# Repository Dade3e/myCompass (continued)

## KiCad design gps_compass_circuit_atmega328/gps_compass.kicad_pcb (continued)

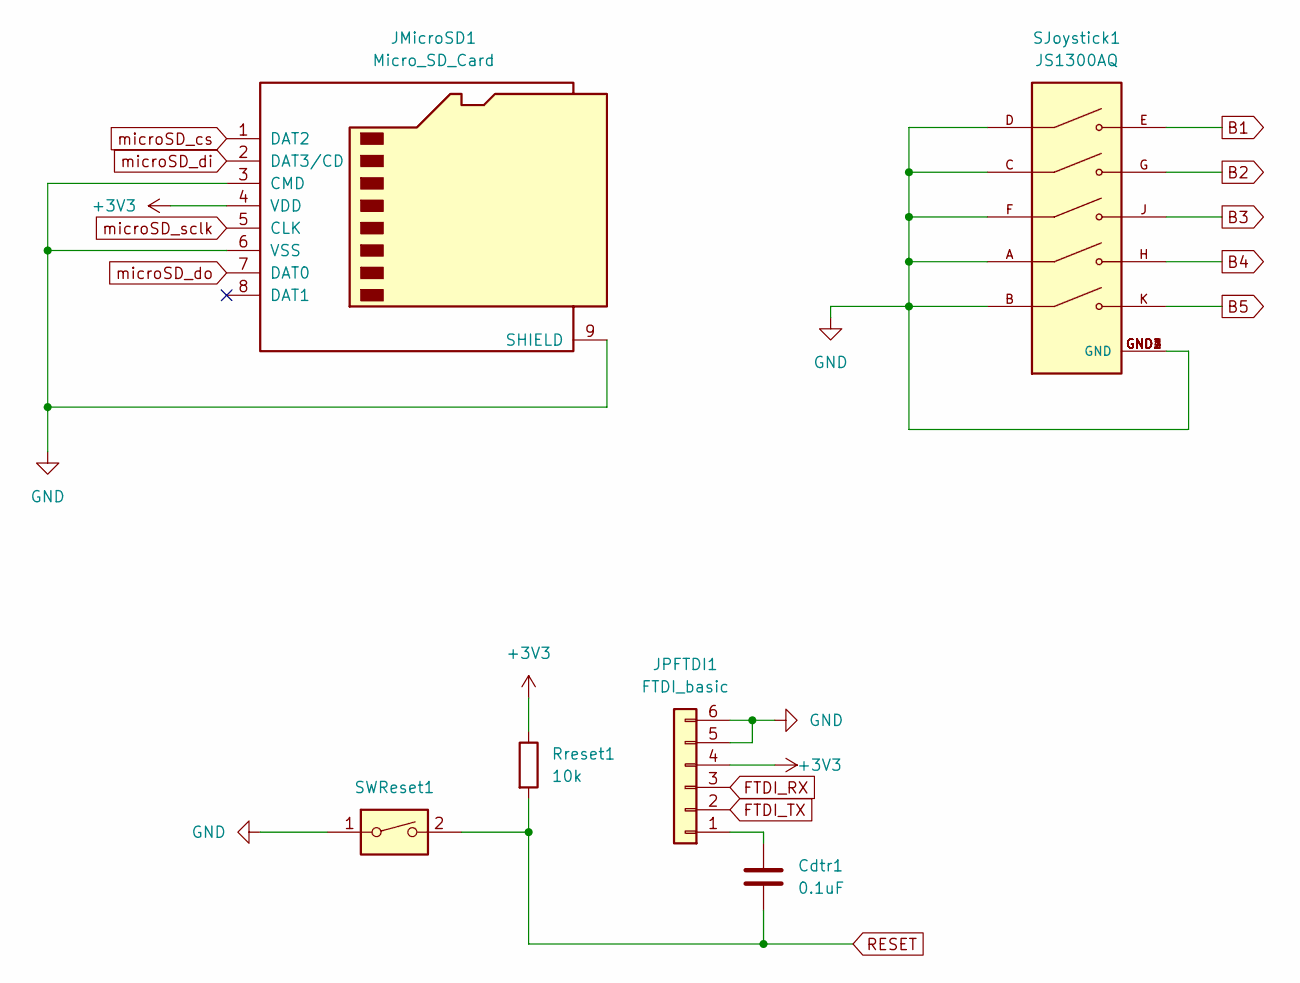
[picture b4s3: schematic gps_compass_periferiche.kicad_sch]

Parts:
Cdtr1: 0.1uF; R_0603_1608Metric
JMicroSD1: Micro_SD_Card; microSD_HC_Molex_47219-2001
JPFTDI1: FTDI_basic; PinSocket_1x06_P2.54mm_Horizontal
Rreset1: 10k; R_0603_1608Metric
SJoystick1: JS1300AQ; SW_JS1300AQ; PARTREV F
SWReset1: SW_Reset; SW_PUSH_6mm

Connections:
+3V3: JMicroSD1.4 (VDD), JPFTDI1.4, Rreset1.1; also elsewhere on the board
B1: SJoystick1.E; also elsewhere on the board
B2: SJoystick1.G; also elsewhere on the board
B3: SJoystick1.J; also elsewhere on the board
B4: SJoystick1.H; also elsewhere on the board
B5: SJoystick1.K; also elsewhere on the board
FTDI_RX: JPFTDI1.3; also elsewhere on the board
FTDI_TX: JPFTDI1.2; also elsewhere on the board
GND: JMicroSD1.3 (CMD), JMicroSD1.6 (VSS), JMicroSD1.9 (SHIELD), JPFTDI1.5, JPFTDI1.6, SJoystick1.A, SJoystick1.B, SJoystick1.C, SJoystick1.D, SJoystick1.F, SJoystick1.GND1 (GND), SJoystick1.GND2 (GND), SJoystick1.GND3 (GND), SJoystick1.GND4 (GND), SWReset1.1; also elsewhere on the board
unnamed: Cdtr1.2, JPFTDI1.1
RESET: Cdtr1.1, Rreset1.2, SWReset1.2; also elsewhere on the board
microSD_cs: JMicroSD1.1 (DAT2); also elsewhere on the board
microSD_di: JMicroSD1.2 (DAT3/CD); also elsewhere on the board
microSD_do: JMicroSD1.7 (DAT0); also elsewhere on the board
microSD_sclk: JMicroSD1.5 (CLK); also elsewhere on the board

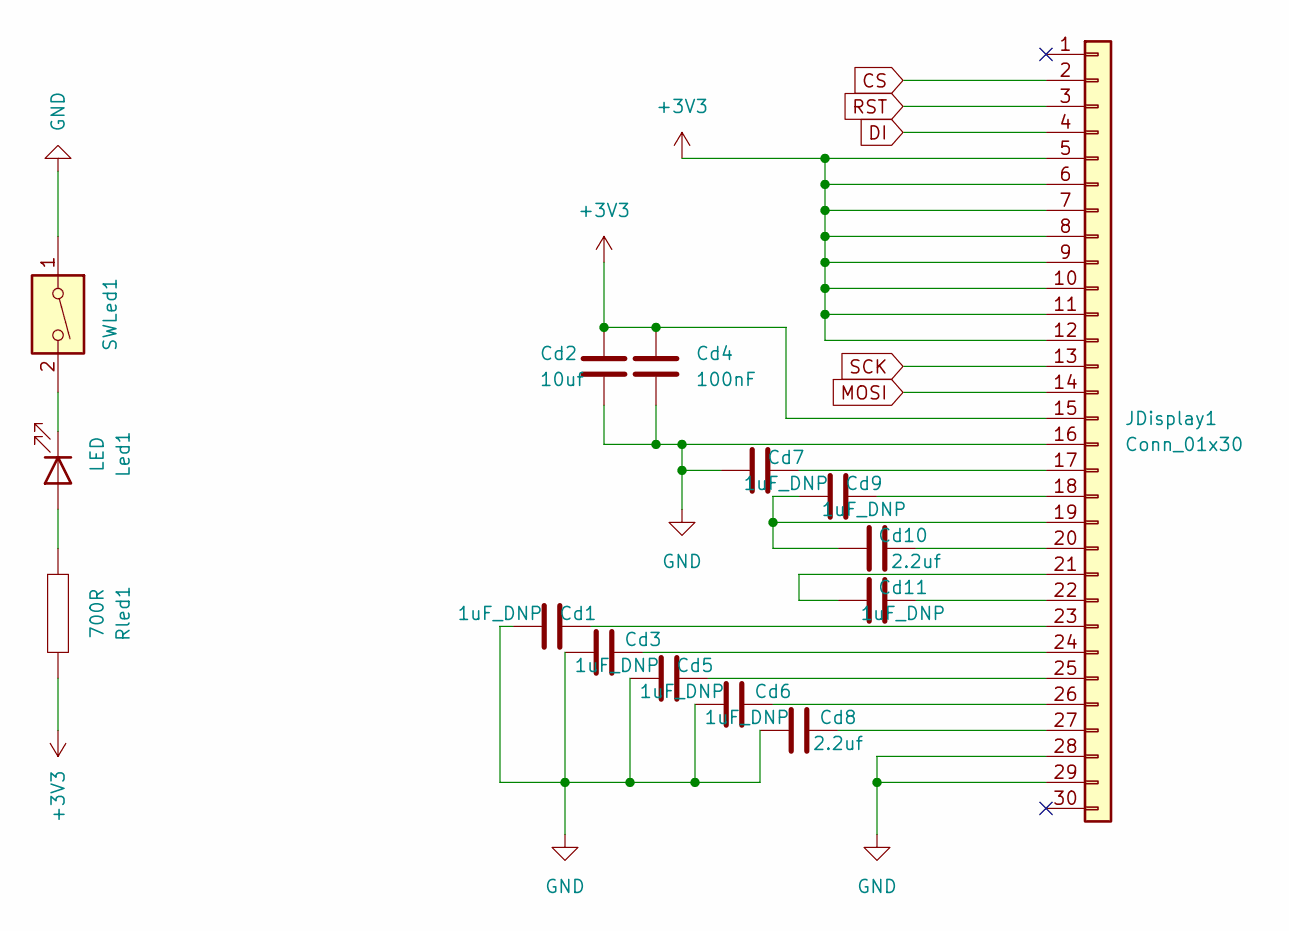
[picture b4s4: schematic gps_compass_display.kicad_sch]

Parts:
Cd1, Cd3, Cd5, Cd6, Cd7, Cd9, Cd11: 1uF_DNP; C_0603_1608Metric
Cd2: 10uf; C_0603_1608Metric
Cd4: 100nF; C_0603_1608Metric
Cd8, Cd10: 2.2uf; C_0603_1608Metric
JDisplay1: Conn_01x30; Hirose_FH12-30S-0.5SH_1x30-1MP_P0.50mm_Horizontal
Led1: LED; LED_D3.0mm
Rled1: 700R; R_0603_1608Metric
SWLed1: SW_Reset; SW_PUSH_6mm

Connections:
+3V3: Cd2.1, Cd4.1, JDisplay1.5, JDisplay1.6, JDisplay1.7, JDisplay1.8, JDisplay1.9, JDisplay1.10, JDisplay1.11, JDisplay1.12, JDisplay1.15, Rled1.2; also elsewhere on the board
CS: JDisplay1.2
DI: JDisplay1.4
GND: Cd1.1, Cd2.2, Cd3.1, Cd4.2, Cd5.1, Cd6.1, Cd7.1, Cd8.1, JDisplay1.16, JDisplay1.28, JDisplay1.29, SWLed1.1; also elsewhere on the board
MOSI: JDisplay1.14
unnamed: Cd1.2, JDisplay1.23
unnamed: Cd3.2, JDisplay1.24
unnamed: Cd5.2, JDisplay1.25
unnamed: Cd6.2, JDisplay1.26
unnamed: Cd7.2, JDisplay1.17
unnamed: Cd8.2, JDisplay1.27
unnamed: Cd9.2, JDisplay1.18
unnamed: Cd9.1, Cd10.1, JDisplay1.19
unnamed: Cd10.2, JDisplay1.20
unnamed: Cd11.1, JDisplay1.21
unnamed: Cd11.2, JDisplay1.22
unnamed: Led1.1 (K), SWLed1.2
unnamed: Led1.2 (A), Rled1.1
RST: JDisplay1.3
SCK: JDisplay1.13

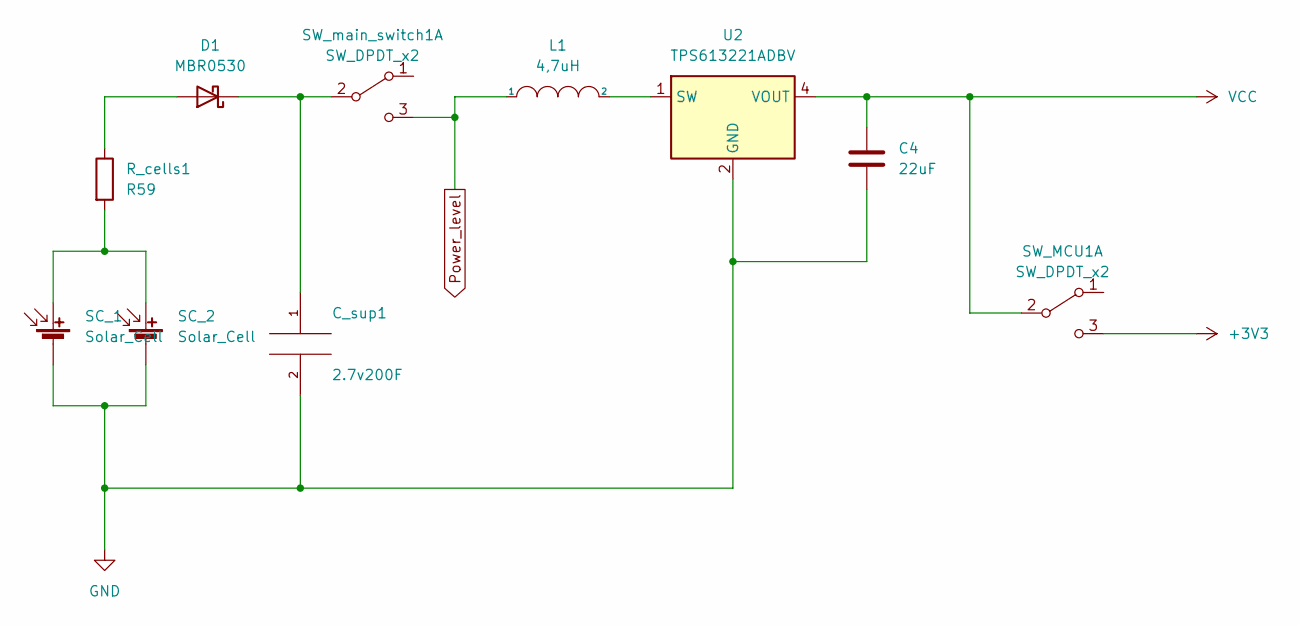
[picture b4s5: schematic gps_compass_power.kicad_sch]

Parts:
C4: 22uF; C_0603_1608Metric
C_sup1: 2.7v200F; C_Rect_L9.0mm_W2.5mm_P7.50mm_MKT
D1: MBR0530; D_SOD-123
L1: 4,7uH; L_0603_1608Metric
R_cells1: R59; R_0603_1608Metric
SC_1, SC_2: Solar_Cell; PinSocket_1x02_P2.54mm_Vertical
SW_MCU1: SW_DPDT_x2; PinSocket_1x03_P2.54mm_Vertical
SW_main_switch1: SW_DPDT_x2; PinSocket_1x03_P2.54mm_Vertical
U2: TPS613221ADBV; SOT-23-5

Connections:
+3V3: SW_MCU1.3 (C); also elsewhere on the board
GND: C4.2, C_sup1.2, SC_1.2 (-), SC_2.2 (-), U2.2 (GND); also elsewhere on the board
unnamed: C_sup1.1, D1.1 (K), SW_main_switch1.2 (B)
unnamed: D1.2 (A), R_cells1.1
unnamed: L1.2, U2.1 (SW)
unnamed: R_cells1.2, SC_1.1 (+), SC_2.1 (+)
Power_level: L1.1, SW_main_switch1.3 (C); also elsewhere on the board
VCC: C4.1, SW_MCU1.2 (B), U2.4 (VOUT); also elsewhere on the board

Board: 2 copper layers, 50 parts (0 on the bottom side), 46 nets, no tracks yet.

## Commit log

2023-04-14 Codici per atmega328 e attiny85
2023-04-14 Rinominati files
2023-04-14 Rimosso file inutilizzato
2023-04-14 Circuito e file idee
2023-04-14 Organizzate librerie
2023-04-20 Aggiornato circuito
2023-04-20 Versione 7 segm
2023-04-20 divisione in parti
2023-04-21 upt circuit
2023-05-02 upd circuit
2023-06-01 Codice per esp32
2023-06-05 Aggiunta versione battery
2023-06-05 Aggiornato con circuito incompleto
2023-06-06 Aggiornamenti vari
2023-06-07 Riposizionati pulsanti
2023-06-07 Controllate piazzole GND
2023-06-07 Aggiornato Gerber
2023-06-07 zip gerber
2023-06-08 Nuova versione, tmp
2023-06-08 migliorati posizionamenti gnd
2023-06-11 Aggiunto led rgb seriale
2023-06-12 Riprestinato led non rgb
2023-06-28 Inizio pregrammazione con pcb
2023-06-29 Vari test
2023-06-29 modifiche varie
2023-06-30 Versione funzionante
2023-06-30 Animazione calibrazione bussola
2023-06-30 Migliorie grafiche
2023-06-30 corretto bug salva punto
2023-07-01 Migliorata parte bussola
2023-07-01 Aggiunto decimale distanza km
2023-07-01 Aggiunto Tetris
    Tetris trovato da questo sito e trasformato per la bussola:
    https://circuitdigest.com/microcontroller-projects/creating-tetris-game-with-arduino-and-oled-display
